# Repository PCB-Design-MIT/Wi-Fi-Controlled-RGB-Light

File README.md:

# Wi-Fi-Controlled-RGB-Light

A demo board for students to learn to solder and debug

Designed by: [Deepta Gupta](https://github.com/deeptag0307), [Winnie Szeto](https://github.com/wszeto9) for IAP 2024

[Interactive BOM](https://htmlpreview.github.io/?https://github.com/PCB-Design-MIT/Wi-Fi-Controlled-RGB-Light/blob/main/bom/ibom.html)

[Interactive Schematic and Layout Viewer](https://kicanvas.org/?github=https%3A%2F%2Fgithub.com%2FPCB-Design-MIT%2FWi-Fi-Controlled-RGB-Light)

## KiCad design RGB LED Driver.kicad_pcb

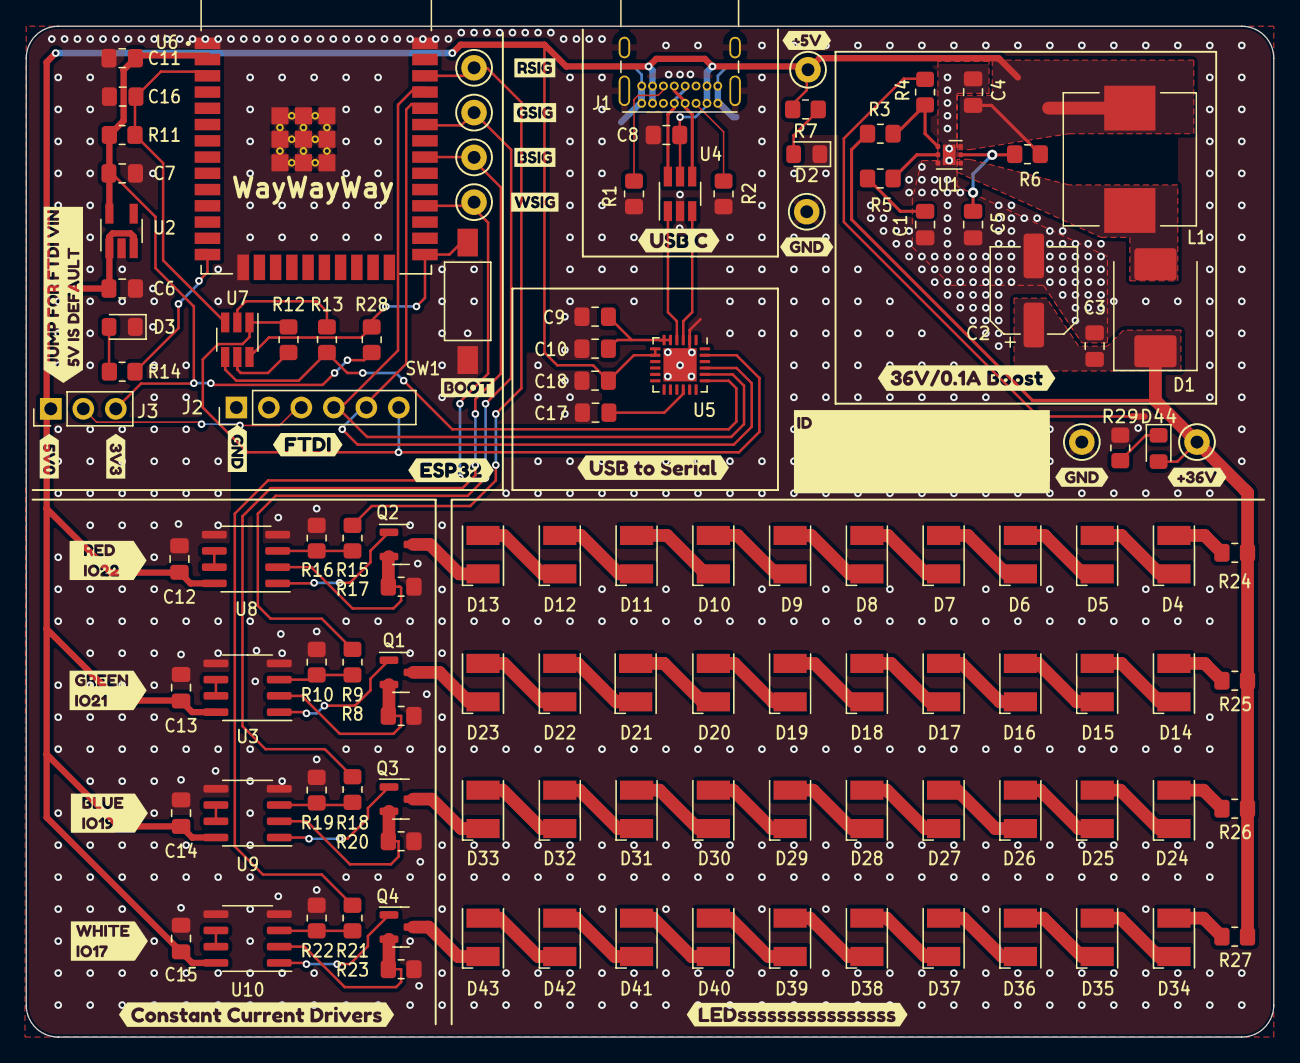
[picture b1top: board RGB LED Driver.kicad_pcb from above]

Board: 2 copper layers, 97.5 x 79.0 mm, 144 parts (0 on the bottom side), 95 nets.

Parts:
C1: 15nF; C_0805_2012Metric_Pad1.18x1.45mm_HandSolder
C2: 10uF/63V; CP_Elec_6.3x5.8
C3, C17: 4.7uF; C_0805_2012Metric_Pad1.18x1.45mm_HandSolder
C4: 10uF; C_0805_2012Metric_Pad1.18x1.45mm_HandSolder
C5, C10, C11, C16, C18: 1uF; C_0805_2012Metric_Pad1.18x1.45mm_HandSolder
C6, C7: 22uF; C_0805_2012Metric_Pad1.18x1.45mm_HandSolder
C8, C9, C12, C13, C14, C15: 100nF; C_0805_2012Metric_Pad1.18x1.45mm_HandSolder
D1: SS36; D_SMC
D2, D3, D44: RED LED; LED_0805_2012Metric_Pad1.15x1.40mm_HandSolder
D4, D5, D6, D7, D8, D9, D10, D11, D12, D13, D14, D15, D16, D17, D18, D19, D20, D21, D22, D23, D24, D25, D26, D27, D28, D29, D30, D31, D32, D33, D34, D35, D36, D37, D38, D39, D40, D41, D42, D43: LED; LED_PLCC-2_3.4x3.0mm_KA
J1: USB4085; USB_C_Receptacle_GCT_USB4085
J2: Conn_01x06_Pin; PinHeader_1x06_P2.54mm_Vertical
J3: Conn_01x03_Pin; PinHeader_1x03_P2.54mm_Vertical
L1: 22uH; L_Wuerth_HCI-1040
NT1: Nettie; NetTie-2_SMD_Pad0.5mm
Q1, Q2, Q3, Q4: AO3400A; SOT-23
R1, R2: 5.1K; R_0805_2012Metric_Pad1.20x1.40mm_HandSolder
R3: 270K; R_0805_2012Metric_Pad1.20x1.40mm_HandSolder
R4, R12, R13, R28: 10K; R_0805_2012Metric_Pad1.20x1.40mm_HandSolder
R5: 86.6K; R_0805_2012Metric_Pad1.20x1.40mm_HandSolder
R6: 1M; R_0805_2012Metric_Pad1.20x1.40mm_HandSolder
R7, R14: 2K; R_0805_2012Metric_Pad1.20x1.40mm_HandSolder
R8, R17, R20, R23: 100R; R_0805_2012Metric_Pad1.20x1.40mm_HandSolder
R9, R15, R18, R21: 33K; R_0805_2012Metric_Pad1.20x1.40mm_HandSolder
R10, R11, R16, R19, R22: 51K; R_0805_2012Metric_Pad1.20x1.40mm_HandSolder
R24, R25, R26, R27: 0R; R_0805_2012Metric_Pad1.20x1.40mm_HandSolder
R29: 300K; R_0805_2012Metric_Pad1.20x1.40mm_HandSolder
SW1: BOOT; SW_SPST_FSMSM
TP1: 5260 (Red); TestPoint_Keystone_5000-5004_Miniature
TP2: 5264 (Yellow); TestPoint_Keystone_5000-5004_Miniature
TP3, TP4: 5261 (Black); TestPoint_Keystone_5000-5004_Miniature
TP5, TP6, TP7, TP8: 5269 (Purple); TestPoint_Keystone_5000-5004_Miniature
U1: TPS61170DRVR; WSON-6-1EP_2x2mm_P0.65mm_EP1x1.6mm
U2: AP2112K-3.3TRG1; SOT-23-5_HandSoldering
U3, U8, U9, U10: LM358; SOIC-8_3.9x4.9mm_P1.27mm
U4: USBLC6-2SC6; SOT-23-6_Handsoldering
U5: CP2102N-A02-GQFN24; QFN-24-1EP_4x4mm_P0.5mm_EP2.6x2.6mm
U6: ESP32-WROOM-32; ESP32
U7: CMXT3904; SOT-23-6_Handsoldering
kibuzzard-6592DDED: G***; kibuzzard-6592DDED
kibuzzard-65932B4E: G***; kibuzzard-65932B4E
kibuzzard-65932B20: G***; kibuzzard-65932B20
kibuzzard-65932B45: G***; kibuzzard-65932B45
kibuzzard-65932B54: G***; kibuzzard-65932B54
kibuzzard-65932F0E: G***; kibuzzard-65932F0E
kibuzzard-65932F1A: G***; kibuzzard-65932F1A
kibuzzard-65932F14: G***; kibuzzard-65932F14
kibuzzard-65932F21: G***; kibuzzard-65932F21
kibuzzard-659323CF: G***; kibuzzard-659323CF
kibuzzard-659324E3: G***; kibuzzard-659324E3
kibuzzard-659325DE: G***; kibuzzard-659325DE
kibuzzard-659433EE: G***; kibuzzard-659433EE
kibuzzard-6593238E: G***; kibuzzard-6593238E
kibuzzard-6593379A: G***; kibuzzard-6593379A
kibuzzard-6594327C: G***; kibuzzard-6594327C
kibuzzard-6594332E: G***; kibuzzard-6594332E
kibuzzard-65932266: G***; kibuzzard-65932266
kibuzzard-65932378, kibuzzard-65932378#2: G***; kibuzzard-65932378
kibuzzard-65932434: G***; kibuzzard-65932434
kibuzzard-65932443: G***; kibuzzard-65932443
kibuzzard-65932491: G***; kibuzzard-65932491
kibuzzard-65932806: G***; kibuzzard-65932806
kibuzzard-65943322: G***; kibuzzard-65943322

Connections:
+3.3V: C7.1, C11.1, J3.3, R11.1, R28.1, U2.5 (VOUT), U6.2 (3V3)
+3V3: C9.1, C10.1, U5.5 (VIO), U5.6 (VDD)
+5V: C4.1, C6.1, C8.1, C12.1, C13.1, C14.1, C15.1, C18.1, J1.A4 (VBUS), J1.A9 (VBUS), J1.B4 (VBUS), J1.B9 (VBUS), J3.1, L1.1, R6.2, R7.1, TP1.1, U1.6 (VIN), U2.1 (VIN), U2.3 (EN), U3.8 (V+), U4.5, U5.7 (REGIN), U5.8 (VBUS), U8.8 (V+), U9.8 (V+), U10.8 (V+)
+36V: C2.1, C3.1, D1.1 (K), D44.2 (A), R3.2, R24.1, R25.1, R26.1, R27.1, TP2.1
/BSig: R18.1, TP7.1, U6.31 (IO19)
/Boost_Converter/FB: R3.1, R4.1, U1.1 (FB)
/Boost_Converter/SW: D1.2 (A), L1.2, U1.4 (SW)
/ESP32/DTR: J2.6, R12.2, U5.23 (DTR), U7.1
/ESP32/FTDI_VIN: J2.3, J3.2
/ESP32/GPIO0: R28.2, SW1.1 (A), U6.25 (IO0), U7.6
/ESP32/RESETn: C16.1, R11.2, U6.3 (EN), U7.3
/ESP32/RTS: R13.1, U5.19 (RTS), U7.4
/ESP32/RX_CP2102_TX_ESP: J2.4, U5.20 (RXD), U6.35 (TXD0)
/ESP32/TX_CP2102_RX_ESP: J2.5, U5.21 (TXD), U6.34 (RXD0)
/GSig: R9.1, TP6.1, U6.33 (IO21)
/LED Driver B/Ifb: Q3.2 (S), R20.1, U9.2 (-)
/LED Driver B/LED-: D33.1 (K), Q3.3 (D)
/LED Driver B/VSet_2V0: R18.2, R19.1, U9.3 (+)
/LED Driver G/Ifb: Q1.2 (S), R8.1, U3.2 (-)
/LED Driver G/LED-: D23.1 (K), Q1.3 (D)
/LED Driver G/VSet_2V0: R9.2, R10.1, U3.3 (+)
/LED Driver R/Ifb: Q2.2 (S), R17.1, U8.2 (-)
/LED Driver R/LED-: D13.1 (K), Q2.3 (D)
/LED Driver R/VSet_2V0: R15.2, R16.1, U8.3 (+)
/LED Driver W/Ifb: Q4.2 (S), R23.1, U10.2 (-)
/LED Driver W/LED-: D43.1 (K), Q4.3 (D)
/LED Driver W/VSet_2V0: R21.2, R22.1, U10.3 (+)
/RSig: R15.1, TP5.1, U6.36 (IO22)
/USB-Serial/USB_N: U4.1, U5.4 (D-)
/USB-Serial/USB_P: U4.3, U5.3 (D+)
/USB_C/CC1: J1.A5 (CC1), R2.1
/USB_C/CC2: J1.B5 (CC2), R1.1
/USB_C/USB_IN_N: J1.A7 (D-), J1.B7 (D-), U4.6
/USB_C/USB_IN_P: J1.A6 (D+), J1.B6 (D+), U4.4
/WSig: R21.1, TP8.1, U6.28 (IO17)
GND: C1.2, C2.2, C3.2, C4.2, C5.2, C6.2, C7.2, C8.2, C9.2, C10.2, C11.2, C12.2, C13.2, C14.2, C15.2, C16.2, C17.2, C18.2, D2.1 (K), D3.1 (K), J1.A1 (GND), J1.A12 (GND), J1.B1 (GND), J1.B12 (GND), J1.S1 (SHIELD), J2.1, NT1.1, R1.2, R2.2, R8.2, R10.2, R16.2, R17.2, R19.2, R20.2, R22.2, R23.2, R29.1, SW1.2 (B), TP3.1, TP4.1, U1.3 (GND), U1.7 (THERMALPAD), U2.2 (GND), U3.4 (V-), U3.5 (+), U4.2, U5.2 (GND), U5.25 (GND), U6.1 (GND), U6.15 (GND), U6.38 (GND), U6.39_1 (GND), U6.39_2 (GND), U6.39_3 (GND), U6.39_4 (GND), U6.39_5 (GND), U6.39_6 (GND), U6.39_7 (GND), U6.39_8 (GND), U6.39_9 (GND), U6.39_10 (GND), U6.39_12 (GND), U8.4 (V-), U8.5 (+), U9.4 (V-), U9.5 (+), U10.4 (V-), U10.5 (+)
unnamed: C1.1, R5.2
unnamed: D2.2 (A), R7.2
unnamed: D3.2 (A), R14.2
unnamed: D4.2 (A), R24.2
unnamed: D4.1 (K), D5.2 (A)
unnamed: D5.1 (K), D6.2 (A)
unnamed: D6.1 (K), D7.2 (A)
unnamed: D7.1 (K), D8.2 (A)
unnamed: D8.1 (K), D9.2 (A)
unnamed: D9.1 (K), D10.2 (A)
unnamed: D10.1 (K), D11.2 (A)
unnamed: D11.1 (K), D12.2 (A)
unnamed: D12.1 (K), D13.2 (A)
unnamed: D14.2 (A), R25.2
unnamed: D14.1 (K), D15.2 (A)
unnamed: D15.1 (K), D16.2 (A)
unnamed: D16.1 (K), D17.2 (A)
unnamed: D17.1 (K), D18.2 (A)
unnamed: D18.1 (K), D19.2 (A)
unnamed: D19.1 (K), D20.2 (A)
unnamed: D20.1 (K), D21.2 (A)
unnamed: D21.1 (K), D22.2 (A)
unnamed: D22.1 (K), D23.2 (A)
unnamed: D24.2 (A), R26.2
unnamed: D24.1 (K), D25.2 (A)
unnamed: D25.1 (K), D26.2 (A)
unnamed: D26.1 (K), D27.2 (A)
unnamed: D27.1 (K), D28.2 (A)
unnamed: D28.1 (K), D29.2 (A)
unnamed: D29.1 (K), D30.2 (A)
unnamed: D30.1 (K), D31.2 (A)
unnamed: D31.1 (K), D32.2 (A)
unnamed: D32.1 (K), D33.2 (A)
unnamed: D34.2 (A), R27.2
unnamed: D34.1 (K), D35.2 (A)
unnamed: D35.1 (K), D36.2 (A)
unnamed: D36.1 (K), D37.2 (A)
unnamed: D37.1 (K), D38.2 (A)
unnamed: D38.1 (K), D39.2 (A)
unnamed: D39.1 (K), D40.2 (A)
unnamed: D40.1 (K), D41.2 (A)
unnamed: D41.1 (K), D42.2 (A)
unnamed: D42.1 (K), D43.2 (A)
unnamed: D44.1 (K), R29.2
unnamed: NT1.2, R4.2
unnamed: Q1.1 (G), U3.1
unnamed: Q2.1 (G), U8.1
unnamed: Q3.1 (G), U9.1
unnamed: Q4.1 (G), U10.1
unnamed: R12.1, U7.5
unnamed: R13.2, U7.2
unnamed: R5.1, U1.2 (COMP)
unnamed: C5.1, R6.1, U1.5 (CTRL)
unnamed: U3.6 (-), U3.7
unnamed: C17.1, U5.16 (VPP)
unnamed: R14.1, U6.14 (IO12)
unnamed: U8.6 (-), U8.7
unnamed: U9.6 (-), U9.7
unnamed: U10.6 (-), U10.7

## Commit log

2024-01-01 backing up shit
2024-01-01 laid out stuff
2024-01-01 added silk for PCBWay to remove customer order
2024-01-01 update gitignore
2024-01-01 neat-ified schematics
2024-01-02 Added annotations, BOM count reduction
    LED indicator resistors edited to save on BOM count
    schematics made more neat, added some labels
2024-01-02 added digikey PNs
2024-01-02 added digikey PNs to all devices
2024-01-02 updated pcb with BOM
2024-01-02 added jumper to FTDI power
2024-01-02 [A02] Initial release
    CP2014 -> CP2012N (BOM cost reduction)
2024-01-02 deleted unused files
2024-01-02 added interactive schematic
2024-01-02 Added jumper into BOM
2024-01-02 cost reduction in BOM
2024-01-17 [A02] Edited resistor values
    R11 to 51K to allow for auto reset
    R3 to 270K for 34V output
